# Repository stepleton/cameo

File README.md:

# Cameo

is a peripheral [cape](https://beagleboard.org/capes) circuit board that allows
the [PocketBeagle](http://beagleboard.org/pocket) single-board computer (which
uses 3.3V digital signals) to interface with 5V digital logic. It is built
around two Texas Instruments [TXS0108EPWR]( http://www.ti.com/product/TXS0108E)
or [TXB0108PWR]( http://www.ti.com/product/TXB0108) 8-bit bidirectional voltage
level translator ICs. Sixteen digital I/O signal lines are available.

Cameo is optimised for applications that take advantage of the two [PRU-ICSS](
https://beagleboard.org/pru) real-time coprocessors built into the chip-like
hybrid circuit that powers the PocketBeagle (a [TI AM3358](
http://www.ti.com/product/AM3358) SoC/[Octavo OSD3358](
https://octavosystems.com/octavo_products/osd335x/) SiP). The digital I/O lines
that pass through Cameo include all fourteen logic lines the PRUs can access
directly in either the input or output direction. The two remaining lines are
one that PRU 0 can use for output only and one it can use for input only, the
latter of which also happens to be the CLOCKIN line for the PRU's "parallel
capture" input mode. Alternatively, all lines may be used bidirectionally via
the AM3358's GPIO modules.

Cameo is "plugboard programmable": a pattern of jumper pads on the cape allow
each signal line to be individually tied/pulled to GND or +5V, or to be
[terminated](https://www.youtube.com/watch?v=rN9zjVK3Nrk) in a variety of ways,
all through installation of appropriate 0603 surface-mount components (or, in a
pinch, solder bridges or small fragments of wire). See the [plugboard pad map](
#plugboard-pad-map) for a diagram showing all of the "plugboard" pads.

## Fair warning

Cameo and associated hardware designs, software materials, and other resources
distributed alongside it are all made available for free with NO WARRANTY OF
ANY KIND. Any system that interfaces with Cameo could suffer malfunction, data
loss, physical damage, or other harms. Some of these effects could be permanent
and/or unrepairable. If you're not prepared to risk these consequences, don't
use Cameo.

## Example applications

* [ Aphid](aphid/),
  a hardware emulator for Apple parallel port hard drives.

## Assembly and installation

Cameo is designed to mount underneath the PocketBeagle, preserving easy access
to the PocketBeagle's soft power button. The pin header for 5V digital I/O is
mounted on the underside of Cameo. With a short ribbon cable like the one in
the photo, the entire lightweight "stack" can dangle from a computer peripheral
port, as long as clearances and the security/fastness of the connector allow.

### Costs

To build a ready-to-use "stack" of your own from parts, you will need (prices
for informational purposes only; many are likely out-of-date):

* A PocketBeagle compact single-board computer ($25)
* A Cameo printed circuit board ($10 per board, **but sold only in packs of 3**
  from [OSH Park](https://www.oshpark.com/shared_projects/51GWu9Kw); shop around
  for deals by uploading the Gerber or KiCad project files in the
  [hardware directory](hardware) to online PCB manufacturers)
* Two TXS0108EPWR bidirectional level translator ICs ([e.g.](
  https://www.digikey.com/short/jr94zw); $1.66 each)
* Four 0.1μF MLCC 0603 surface mount capacitors ([e.g.](
  https://www.digikey.com/short/jr9znz); $0.10 each)
* One 240kΩ 0603 surface mount resistor ([e.g.](
  https://www.digikey.com/short/jrvd8z); $0.10 for just one)
* One 2x13 0.1" pitch pin header ([e.g.](https://www.digikey.com/short/jr9439);
  plastic shroud at your discretion; $0.30)
* Two 2x18 0.1" pitch pin headers ([e.g.](https://www.digikey.com/short/jr94b9);
  $0.69 each)
* Two 2x18 0.1" pitch sockets ([e.g.](https://www.digikey.com/short/jr94rq);
  $2.06 each)
* microSD memory card, 4GB or more, class 10 or better ($7 or so)
* Jumper and termination 0603 surface-mount components for I/O pins as required
  by your application (assuming the [Aphid](aphid/) configuration with 3 0Ω
  jumpers ([e.g.](https://www.digikey.com/short/jr9m80)) and 13 100Ω inline
  terminating resistors ([e.g.](https://www.digikey.com/short/j1rr2w)), $0.53
  altogether; jumpers are free if you make your own from scrap wire)

costing $52.15 in total. If you are willing to bond the PocketBeagle and Cameo
together permanently, you can omit the 2x18 sockets and save a bit over $4.

Some applications may benefit from adapting the 26-pin header on the bottom of
Cameo to a 25-pin DB-25 plug connector. To make this adaptor, you can use:

* 2x13 0.1" pitch socket with IDC crimp termination ([e.g.](
  https://www.digikey.com/short/jrbw3d), $0.58)
* DB-25 plug connector with IDC crimp termination ([e.g.](
  https://www.digikey.com/short/jrb2dj), $2.33)
* A short length (around 5cm) of 26-pin ribbon cable. ([e.g.](
  https://www.digikey.com/short/jrb2rr); $1.28 for a foot, ideally scrounged
  from a junk drawer for free)

adding to an additional $4.19.

### Assembly

Cameo is not an ideal starter project for hobbyists new to soldering
surface-mounted components; on the other hand, it doesn't have too many of
them, and they're not very tightly packed. The following diagram shows the
locations of essential SMD components on Cameo:

More SMD components will be required to set up the "plugboard" that connects
PocketBeagle signal lines to pins on the 5V I/O header. The specific nature and
configuration of these components are application-specific. See the
[introduction](#cameo) and the [plugboard pad map](#plugboard-pad-map) for more
details of the plugboard.

When assembling the Cameo board, it may be advisable to place the two voltage
translator ICs first, followed by the discrete SMD components and then by the
through-hole headers/connectors. **Remember, Cameo expects to be slung
underneath the PocketBeagle, so the 5V I/O header (centre) should emerge from
the bottom of the board, while the headers (or sockets) for connecting to the
PocketBeagle should emerge from the top.**

To connect to Cameo, the PocketBeagle will need sockets (or headers) emerging
from the **bottom** of its PCB. When mating Cameo to the PocketBeagle, be
certain of the correct orientation: if Cameo is orientated as shown above, the
USB connector on the PocketBeagle should be visible and pointing leftward.

Refer to online tutorials for making ribbon cable assemblies with IDC
connectors ([e.g.](https://startingelectronics.org/articles/IDC-ribbon-cable/))
to build an adaptor for the 5V I/O header. In general, it's best for the cable
between the two connectors to be as short as possible.

## Header pinout

The following pinout diagram represents Cameo's 26-pin 5V I/O header as viewed
from the underside of the Cameo PCB, with the PocketBeagle's USB connector
pointing upward.

| GPIO | PRU | PB pin | |   Name | I/O pin | I/O pin | Name   | | PB pin | PRU | GPIO |
|-----:|----:|-------:|-|-------:|:-------:|:-------:|:-------|-|:-------|:----|:-----|
|      |     |        | | _n/c_  |  **1**  |  **2**  |  PEX3  | | P1.35  | 1 ⇆ | 2.24 |
| 1.10 | ⇆ 1 |  P1.32 | |  PEX1  |  **3**  |  **4**  | \PSTRB | | P2.9   | 0 ← | 0.15 |
| 1.11 | ⇆ 1 |  P1.30 | | PR/\W  |  **5**  |  **6**  | \PBSY  | | P2.35  | 1 ⇆ | 2.22 |
| 2.25 | ⇆ 1 |   P1.4 | |  PEX2  |  **7**  |  **8**  | \PCMD  | | P1.2   | 1 ⇆ | 2.23 |
| 3.14 | ⇆ 0 |  P1.36 | |   PD0  |  **9**  | **10**  |\PPARITY| | P2.24  | 0 → | 1.12 |
| 3.15 | ⇆ 0 |  P1.33 | |   PD1  |  **11** | **12**  |   ⏚    | |        |     |      |
|      |     |        | |  _n/c_ |  **13** | **14**  |   ⏚    | |        |     |      |
| 3.16 | ⇆ 0 |  P2.32 | |   PD2  |  **15** | **16**  | _n/c_  | |        |     |      |
|      |     |        | |    ⏚   |  **17** | **18**  |  PD3   | | P2.30  | 0 ⇆ | 3.17 |
|      |     |        | |    ⏚   |  **19** | **20**  |  PD4   | | P1.31  | 0 ⇆ | 3.18 |
| 3.19 | ⇆ 0 |  P2.34 | |   PD5  |  **21** | **22**  |   ⏚    | |        |     |      |
| 3.20 | ⇆ 0 |  P2.28 | |   PD6  |  **23** | **24**  |   ⏚    | |        |     |      |
| 3.21 | ⇆ 0 |  P1.29 | |   PD7  |  **25** | **26**  |   ⏚    | |        |     |      |

The names of the 5V I/O pins reflect one of the example applications and should
be considered arbitrary. Pins marked _n/c_ connect to nothing; pins marked ⏚
are tied to ground.

The "PB pin" column shows which PocketBeagle header pin connects to Cameo's 5V
I/O header (through the 3.3V ⇆ 5V bidirectional voltage level translator ICs).

The "PRU" columns show which of the two PRU-ICSS real-time coprocessors in the
AM3358 are connected to each pin. A ⇆ symbol means that the corresponding
PocketBeagle pin can be configured either as an input to or an output of the
PRU; the ← and → symbols mean that the pin can only be a PRU input or output
respectively. Pins PD0-PD7 in particular map to PRU 0 GPIO bits 0-7.

The "GPIO" columns show how the pins correspond to I/O bits in the AM3358's
GPIO modules ("3.21" means module 3, bit 21). All pins may be accessed in any
direction through the GPIO subsystem.

For more detailed connectivity information, refer to the expansion header
tables in the [PocketBeagle reference manual](
https://github.com/beagleboard/pocketbeagle/wiki/System-Reference-Manual#71_Expansion_Header_Connectors).

Note finally that if an ordinary ribbon cable is used in an adaptor that
connects the 5V I/O header to a DB-25 plug connector, the pin numbering
patterns for both are different:

| DB-25 pin  | 1 | 2 | 3 | 4 | 5 |  6 |  7 |  8 |  9 | 10 | 11 | 12 | 13 |
|------------|---|---|---|---|---|----|----|----|----|----|----|----|----|
| Header pin | 1 | 3 | 5 | 7 | 9 | 11 | 13 | 15 | 17 | 19 | 21 | 23 | 25 |

| DB-25 pin  | 14 | 15 | 16 | 17 | 18 | 19 | 20 | 21 | 22 | 23 | 24 | 25 |
|------------|----|----|----|----|----|----|----|----|----|----|----|----|
| Header pin |  2 |  4 |  6 |  8 | 10 | 12 | 14 | 16 | 18 | 20 | 22 | 24 |

## Plugboard pad map

This diagram shows a top-side view of Cameo. (In this view, the through-holes
for the 26-pin 5V I/O header (centre) are "flipped" about the header's long
(horizontal) axis, since the pins emerge from the underside of the board.)

The installation of jumpers, resistors, or other 0603 surface mount components
on each set of five pads shaped like ⠾, ⠻, or ⠷ determines whether and how the
labelled pin connects (through the voltage translator ICs) to the PocketBeagle.

## Development

Cameo was designed with [KiCad](http://kicad-pcb.org/) 4.  Project files and
derived products (Gerber files, etc.) are kept in the [hardware](hardware/)
subdirectory.

## Other notes

To the fullest extent possible, Cameo is released into the public domain.
Nobody owns Cameo.

## Acknowledgements

It would not have been possible for me to design Cameo without the help of the
following people and resources:

* Michael Welling's [pocketbeagle-cape-template](
  https://github.com/mwelling/pocketbeagle-cape-template).
* The [Sitara Processors Forum](https://e2e.ti.com/support/arm/sitara_arm) on
  the [TI E2E Community](https://e2e.ti.com/).
* Anonymous friends.

-- [_Tom Stepleton_](mailto:stepleton@gmail.com), 11 August 2018, London

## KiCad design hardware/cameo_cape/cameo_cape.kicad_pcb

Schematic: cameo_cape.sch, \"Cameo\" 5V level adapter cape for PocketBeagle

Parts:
C1, C2, C3, C4: 0.1; C_0603_HandSoldering
JP1, JP2, JP16, JP19, JP20, JP21, JP22, JP23, JP24, JP25, JP26, JP27, JP28, JP29, JP30, JP31: Jumper_NO_Small; R_0603_HandSoldering
JP3, JP4, JP5, JP6, JP7, JP8, JP9, JP10, JP11, JP12, JP13, JP14, JP15, JP17, JP18, JP32: Jumper_NC_Small; R_0603_HandSoldering
P1, P2: TH-2X18-(35MIL-DIA)-W_O-SILK
P3: CONN_02X13; Pin_Header_Straight_2x13
R1: 240K; R_0603_HandSoldering
R2, R3, R4, R5, R6, R7, R8, R9, R10, R11, R12, R13, R14, R15, R16, R17: R_Small; R_0603_HandSoldering
U1, U2: TXS0108E_PW_20; TXS0108EPWR

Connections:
/(U1.A1)PWM0A: P1.36, U2.1 (A1)
/(U1.A2)PRU-0.1: P1.33, U2.3 (A2)
/(U1.A3)PRU-0.4: P1.31, U2.6 (A5)
/(U1.A4)SPI1.CS: P2.31
/(U1.A8)AIN0~1.8V: P1.19
/(U1.A10)I2C2.SCL: P1.28
/(U1.A11)I2C1.SDA: P2.11
/(U1.A12)UART0.RX: P1.32, U1.7 (A6)
/(U1.A13)SPI0.CLK: P1.8
/(U1.A14)SPI0.CS: P1.6
/(U1.B1)PRU-0.3: P2.30, U2.5 (A4)
/(U1.B2)PRU-0.2: P2.32, U2.4 (A3)
/(U1.B3)PRU-0.5: P2.34, U2.7 (A6)
/(U1.B4)PRU-0.16: P1.20
/(U1.B6)AIN2~1.8V: P1.23
/(U1.B7)VREF+: P1.18
/(U1.B8)AIN1~1.8V: P1.21
/(U1.B9)VREF-: P1.17
/(U1.B10)I2C2.SDA: P1.26
/(U1.B11)I2C1.SCL: P2.9, U1.3 (A2)
/(U1.B12)UART0.TX: P1.30, U1.8 (A7)
/(U1.B13)SPI0.MISO: P1.10
/(U1.B14)SPI0.MOSI: P1.12
/(U1.C3)PRU-0.6: P2.28, U2.8 (A7)
/(U1.C4)PRU-0.7: P1.29, U2.9 (A8)
/(U1.C5)SPI1.CLK: P2.29
/(U1.C6)AIN3~1.8V: P1.25
/(U1.C7)AIN4~1.8V: P1.27
/(U1.C12)SPI1.MISO: P2.27
/(U1.C13)SPI1.MOSI: P2.25
/(U1.E1): P1.4, U1.6 (A5)
/(U1.F1): P1.35, U1.9 (A8)
/(U1.F2)AIN6~3.3V: P1.2, U1.5 (A4)
/(U1.F3)AIN5~3.3V: P2.35, U1.4 (A3)
/(U1.L14)USB1.ID: P1.13
/(U1.L15)USB1.D+: P1.11
/(U1.L16)USB1.D-: P1.9
/(U1.M14)USB1.DRVVBUS: P1.3
/(U1.M15)USB1.VBUS: P1.5
/(U1.N13)AIN7~1.8V: P2.36
/(U1.N14): P2.8
/(U1.P5)GPIO-0.23: P2.3
/(U1.P6): P2.24, U1.1 (A1)
/(U1.P7)PRU-0.15: P2.18
/(U1.P12)PWM1A: P2.1
/(U1.P15)UART4.RX: P2.5
/(U1.R5)GPIO-0.26: P1.34
/(U1.R6): P2.33
/(U1.R7): P2.20
/(U1.R11)RESET#: P2.26, R1.1, U1.10 (OE), U2.10 (OE)
/(U1.R13): P2.10
/(U1.R15): P2.4
/(U1.R16)UART4.TX: P2.7
/(U1.T5): P2.19
/(U1.T6)PRU-0.14: P2.22
/(U1.T7): P2.17
/(U1.T11)PWR.BTN: P2.12
/(U1.T15): P2.6
/(U1.T16): P2.2
/BAT.TEMP: P2.16
/PD0: JP4.1, U2.20 (B1)
/PD1: JP5.1, U2.18 (B2)
/PD2: JP6.1, U2.17 (B3)
/PD3: JP11.2, U2.16 (B4)
/PD4: JP10.2, U2.15 (B5)
/PD5: JP7.1, U2.14 (B6)
/PD6: JP8.1, U2.13 (B7)
/PD7: JP9.1, U2.12 (B8)
/PEX1: JP1.1, U1.14 (B6)
/PEX2: JP3.1, U1.15 (B5)
/PEX3: JP16.2, U1.12 (B8)
/PR/~W: JP2.1, U1.13 (B7)
/~PBSY: JP14.2, U1.17 (B3)
/~PCMD: JP13.2, U1.16 (B4)
/~PPARITY: JP12.2, U1.20 (B1)
/~PSTRB: JP15.2, U1.18 (B2)
GND: C1.2, C2.2, C3.2, C4.2, JP17.1, JP18.1, JP19.1, JP20.1, JP21.1, JP22.1, JP23.1, JP24.1, JP25.1, JP26.1, JP27.1, JP28.1, JP29.1, JP30.1, JP31.1, JP32.1, P1.15, P1.16, P1.22, P2.15, P2.21, P3.12, P3.14, P3.17, P3.19, P3.22, P3.24, P3.26, R1.2, U1.11 (GND), U2.11 (GND)
unnamed: JP1.2, JP17.2, P3.3, R2.2
unnamed: JP10.1, JP26.2, P3.20, R11.2
unnamed: JP11.1, JP27.2, P3.18, R12.2
unnamed: JP12.1, JP28.2, P3.10, R13.2
unnamed: JP13.1, JP29.2, P3.8, R14.2
unnamed: JP14.1, JP30.2, P3.6, R15.2
unnamed: JP15.1, JP31.2, P3.4, R16.2
unnamed: JP16.1, JP32.2, P3.2, R17.2
unnamed: JP2.2, JP18.2, P3.5, R3.2
unnamed: JP3.2, JP19.2, P3.7, R4.2
unnamed: JP4.2, JP20.2, P3.9, R5.2
unnamed: JP5.2, JP21.2, P3.11, R6.2
unnamed: JP6.2, JP22.2, P3.15, R7.2
unnamed: JP7.2, JP23.2, P3.21, R8.2
unnamed: JP8.2, JP24.2, P3.23, R9.2
unnamed: JP9.2, JP25.2, P3.25, R10.2
SYS_5V: C2.1, C4.1, P1.24, P2.13, R2.1, R3.1, R4.1, R5.1, R6.1, R7.1, R8.1, R9.1, R10.1, R11.1, R12.1, R13.1, R14.1, R15.1, R16.1, R17.1, U1.19 (V), U2.19 (V)
USB_DC: P1.7
VDD_3V3B: C1.1, C3.1, P1.14, P2.23, U1.2 (VCCA), U2.2 (VCCA)
VDD_5V: P1.1
VIN.BAT: P2.14

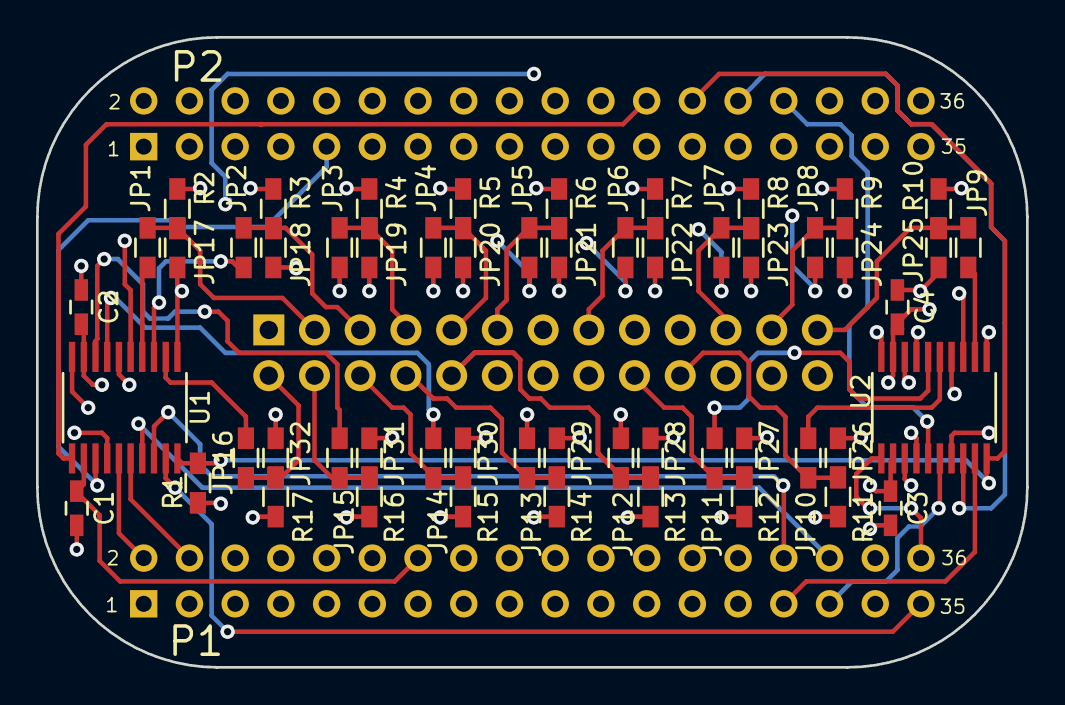
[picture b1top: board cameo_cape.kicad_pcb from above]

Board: 4 copper layers, 55.0 x 35.0 mm, 58 parts (0 on the bottom side), 52 nets.

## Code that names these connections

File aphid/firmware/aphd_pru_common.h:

/* Apple parallel port storage emulator for Cameo
 *
 * Forfeited into the public domain with NO WARRANTY. Read LICENSE for details.
 *
 * This file: constants and other shared information for both PRU programs.
 *
 * Comments may refer to various manuals by abbreviations:
 *    TRM: AM335x Technical Reference Manual
 *    PRG: AM335x PRU Reference Guide
 */

#ifndef APHD_PRU_COMMON_H_
#define APHD_PRU_COMMON_H_


/* //////////////////////
//// I/O PIN ALIASES ////
////////////////////// */

/* Control lines are unidirectional, so we can refer to them via constants
 * whether we are retrieving or sending data. */

#define pBSY      r30.t8
#define psBSY     "r30.t8"
#define ppBSY     8

#define pCMD      r31.t9
#define psCMD     "r31.t9"
#define ppCMD     9

#define pPARITY   r30.t14
#define psPARITY  "r30.t14"
#define ppPARITY  14

#define pRW       r31.t15    /* NOTE: This signal is PEX2 on the schematic, */
#define psRW      "r31.t15"  /* not PR/\W. */
#define ppRW      15

#define pSTRB     r31.t16
#define psSTRB    "r31.t16"
#define ppSTRB    16


/* /////////////////////////
//// INTERRUPT HANDLING ////
///////////////////////// */

#define ePRU0to1 16U  /* System event for interrupts from PRU0 to PRU1 */
#define ePRU1to0 17U  /* System event for interrupts from PRU1 to PRU0 */
#define ePRU1toARM 18U  /* System event for interrupts from PRU1 to ARM */
#define eARMtoPRU1 19U  /* System event for interrputs from ARM to PRU1 */
/* Note: The Linux kernel device tree for the Beagles specify system events
 * 16 and 17 for RPMsg kicks between PRU0 and the ARM, and system events
 * 18 and 19 for RPMsg kicks between PRU1 and the ARM. Events 16 and 18 go
 * to the ARM; events 17 and 19 go to the PRU. */

#define sPRU0to1 16U + ePRU0to1  /* For raising a PRU0 to PRU1 system event */
#define sPRU1to0 16U + ePRU1to0  /* For raising a PRU1 to PRU0 system event */
#define sARMtoPRU1 16U + eARMtoPRU1  /* For raising an ARM to PRU1 sysevent */

#define iAnyToPRU1 31U  /* R31 bit indicating any interrupt to PRU1 */
#define iPRU1to0 30U    /* R31 bit indicating an interrupt from PRU1 to PRU0 */
/* Note: The resource table must ultimately map:
 *   system event ePRU0to1 to host interrupt (iAnyToPRU1 - 30),
 *   system event ePRU1to0 to host interrupt (iPRU1to0 - 30), and
 *   system event eARMtoPRU1 to host interrupt (iAnyToPRU1 - 30)
 * for these definitions to be correct. */


/* ////////////////////
//// CONST ALIASES ////
//////////////////// */

/* Aliases for various const registers (PRG 5.2.1). */

#define cINTC    c0   /* Pointer to PRU INTC */
#define cCONFIG  c4   /* Pointer to PRU_SYSCFG */
#define cSHARED  c28  /* Pointer to shared PRU RAM */

/* Aliases for offsets from various const registers. */

#define oINTC_SICR 0x24  /* cINTC offset to SICR register */


/* /////////////////////////
//// DATA PUMP COMMANDS ////
///////////////////////// */

#define dREAD    0x00  /* Read a block of data from the data lines */
#define dWRITE   0x01  /* Write a block of data to the data lines */
#define dINVALID 0x80  /* An intentional nonsense command, used for resets */


#endif  /* APHD_PRU_COMMON_H_ */

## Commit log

2018-07-25 Delay message in README.md
2018-08-12 Cameo and Aphid full initial commit
2018-08-12 Correct resistor value in SMD component layout images.
2018-08-13 Correct the year in the main README.
2018-08-13 Correct the year in the Aphid README.
2018-10-04 Cameo/Aphid September 2018 update
2018-10-20 Update for the 2018-10-07 BeagleBoard.org image
    Plus a small progress report on signal termination for longer cables.
2018-12-07 Add 100Ω inline terminating resistors to most Aphid signal lines.
2019-11-06 Debian 9.9 disk image
2020-01-12 profile.py => python3; "conclusion" mechanism for restarting emulator from the Apple.
2021-01-17 Cameo/Aphid drive image selector: initial release
2021-01-17 Cosmetic Selector manual fixes
2021-01-23 Cameo/Aphid: Fix overly picky PRU1 state machine timing
    Waiting for a particular coincidence of \PCMD high and PR/\W low could lock up PRU0 for
    nearly 11 seconds if non-handshake activity on the control lines wiggled \PCMD and PR/\W
    together in a confusing way (specifically, in a way that left PR/\W high or had PR/\W go
    from low to high very quickly). The initialisation routine for the parallel interface
    card was prone to generating these toxic wiggles, but owing to vagaries of signal
    propagation and other electrical mysteries, a Cameo/Aphid device would only be affected
2021-01-23 Cameo/Aphid selector: HelloBootDrive interprets $00 drive IDs correctly on Lisa 2/10s
    012345678 012345678 012345678 012345678 012345678 012345678 012345678 012345678
    HelloBootDrive now converts device ID $00 to $02 on Lisa 2/10 systems, fixing a
    bug where the Selector would not believe on startup that the built-in parallel port
    (which it knows as $02) had a Cameo/Aphid attached.
2021-01-23 Cameo/Aphid selector: HelloBootDrive interprets $00 drive IDs as $02 on 2/10s
    HelloBootDrive now converts device ID $00 to $02 on Lisa 2/10 systems, fixing a
    bug where the Selector would not believe on startup that the built-in parallel
    port (which it knows as $02) had a Cameo/Aphid attached.
2021-01-24 Cameo/Aphid: New image, update docs, update installation scripts
2021-01-24 Cameo/Aphid Selector: 0.6, adds a S(elect command, docs updated
    Also renames the scripting command `Load` to `Read` to align with other
    nomenclature for usage of the key/value cache.
2021-01-30 Cameo/Aphid drive image selector: adds a screensaver, docs updated
2021-01-30 Cameo/Aphid drive image selector: add documentation screensaver image
2021-01-30 Cameo/Aphid drive image selector: update a screen depiction in manual
2021-01-30 Cameo/Aphid drive image selector: Final 0.7 manual corrections
2021-02-02 Cameo/Aphid: Device tree overlay + firmware autoload for fast boot
2021-02-06 Cameo/Aphid: support for ProFile-10 and nonstandard size drive images
2021-02-12 Cameo/Aphid: correct double-negative in firmware loading
2021-02-15 Cameo/Aphid: "No-timeout" PRU0 operation for better MacWorks compatibility
2021-02-16 Cameo/Aphid: Selector v0.8 and miscellaneous other convenience items
    Selector: Bounded status string printing to avoid screen mess if the Cameo/Aphid
    goes offline.
    Filesystem plugin: Addition of a 'mx' command for creating arbitrarily-sized
    drive images.
    Utility: addition of a diagnostic script for snooping on PRU1 by peeking into
    ARM/PRU shared memory space.
2021-02-24 Cameo/Aphid: Correct mis-assembly of the Selector
    The Selector floppy disk image should include the ProFile I/O library
    The Selector hard drive image should not
    It had been reversed, but it's corrected now
2021-02-27 Cameo/Aphid: Selector disk images now for both kinds of floppy
2021-02-27 Cameo/Aphid: Add a plugin that makes it easy to restore an overwritten Selector
2021-02-28 Cameo/Aphid Selector 0.9: image creation size option, and more
    Catalogue display shows the sizes of drive images
    Bugfix for text input setup when editing long strings
2021-02-28 Cameo/Aphid Selector 0.9: manual update
2021-02-28 Cameo/Aphid Selector 0.9: manual "picture" update
2021-02-28 Cameo/Aphid Selector 0.9: February is not a leap year
2021-03-28 Cameo/Aphid Selector 1.0: power button, floppy eject, autoboot password, bugfixes
2021-03-28 Cameo/Aphid Selector 1.0: fix missing documentation item
2021-06-19 Apple /// compatibility; Big Sur USB compatibility
2021-06-20 Correct credits in Aphid README
2021-09-08 added arcanebyte designs

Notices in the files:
parts and their libraries:
Copyright 2016 Accelerated Designs. All rights reserved.
